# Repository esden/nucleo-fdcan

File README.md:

This repository contains FDCAN addon boards for Nucleo

Most Nucleo boards have the same pinout for the CAN capable microcontrollers.

The adapter board uses PD0 and PD1 pins for FDCAN TX and RX pins.

Additionally PD3 is used for the STBY pin control.

You plug it into the left connector on the Nucleo board.

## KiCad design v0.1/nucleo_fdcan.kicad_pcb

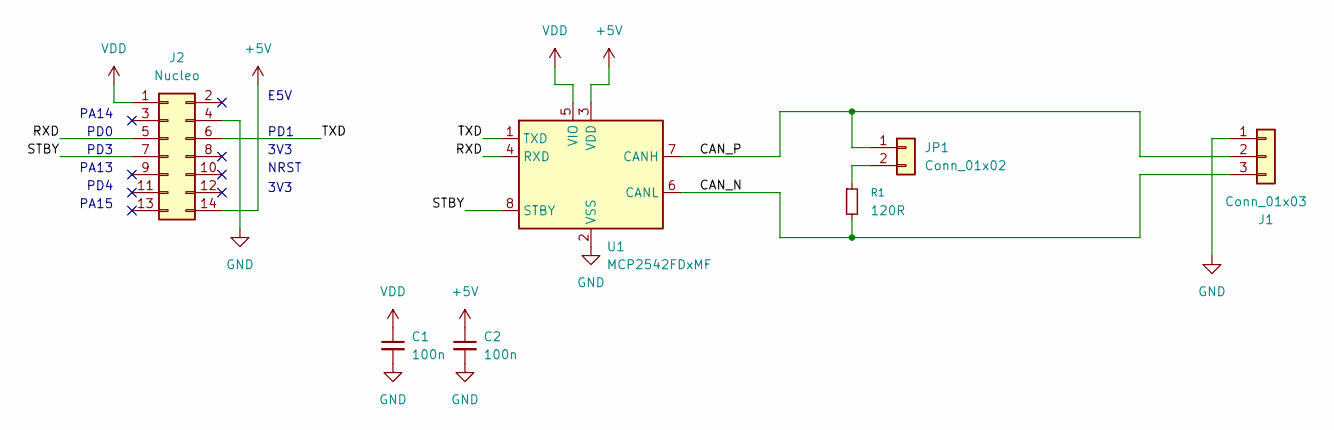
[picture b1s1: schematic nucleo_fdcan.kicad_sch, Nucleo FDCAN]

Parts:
C1, C2: 100n; C_0402_1005Metric
J1: Conn_01x03; Molex_SL_171971-0003_1x03_P2.54mm_Vertical
J2: Nucleo; PinSocket_2x07_P2.54mm_Vertical
JP1: Conn_01x02; PinHeader_1x02_P2.54mm_Horizontal
R1: 120R; R_0402_1005Metric
U1: MCP2542FDxMF; DFN-8-1EP_3x3mm_P0.65mm_EP1.55x2.4mm

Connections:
+5V: C2.1, J2.14, U1.3 (VDD)
/CAN_N: J1.3, R1.2, U1.6 (CANL)
/CAN_P: J1.2, JP1.1, U1.7 (CANH)
/RXD: J2.5, U1.4 (RXD)
/STBY: J2.7, U1.8 (STBY)
/TXD: J2.6, U1.1 (TXD)
GND: C1.2, C2.2, J1.1, J2.4, U1.2 (VSS), U1.9 (VSS)
unnamed: JP1.2, R1.1
VDD: C1.1, J2.1, U1.5 (VIO)

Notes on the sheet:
PA13
PD0
3V3
PD3
PD4
E5V
PA14
PA15
NRST
PD1

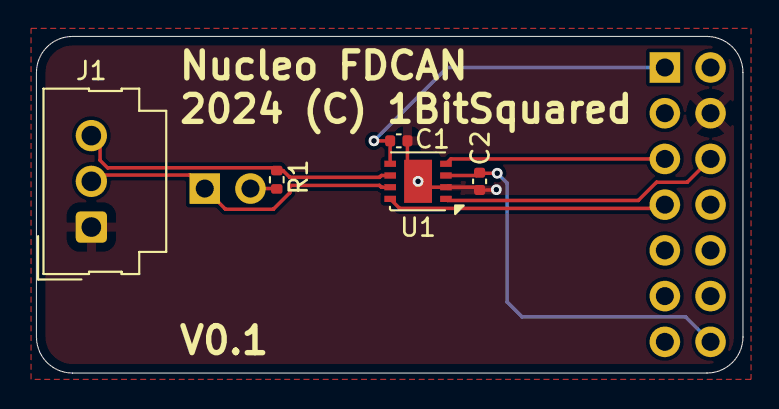
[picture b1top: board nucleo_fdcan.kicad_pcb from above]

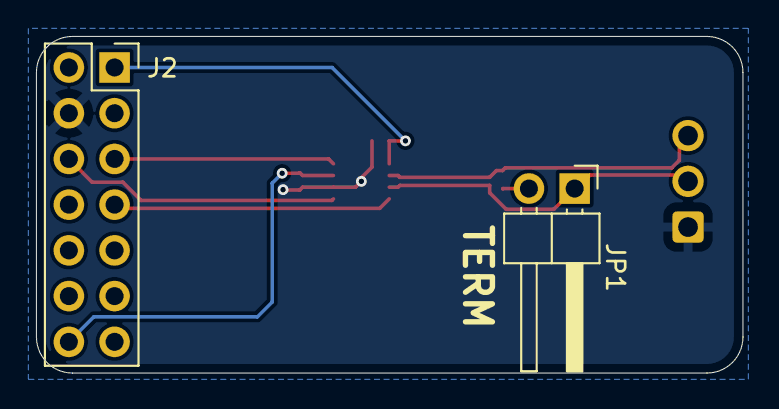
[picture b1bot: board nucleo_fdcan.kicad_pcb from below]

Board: 2 copper layers, 39.2 x 18.7 mm, 7 parts (2 on the bottom side), 9 nets.

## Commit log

2025-06-09 Initial commit.
2025-06-09 Added a README

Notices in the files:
v0.1/nucleo_fdcan.kicad_pcb:
License: CC-BY-SA 4.0
v0.1/nucleo_fdcan.kicad_sch:
(C) 2025 1BitSquared
(C) 2025 Piotr Esden-Tempski
